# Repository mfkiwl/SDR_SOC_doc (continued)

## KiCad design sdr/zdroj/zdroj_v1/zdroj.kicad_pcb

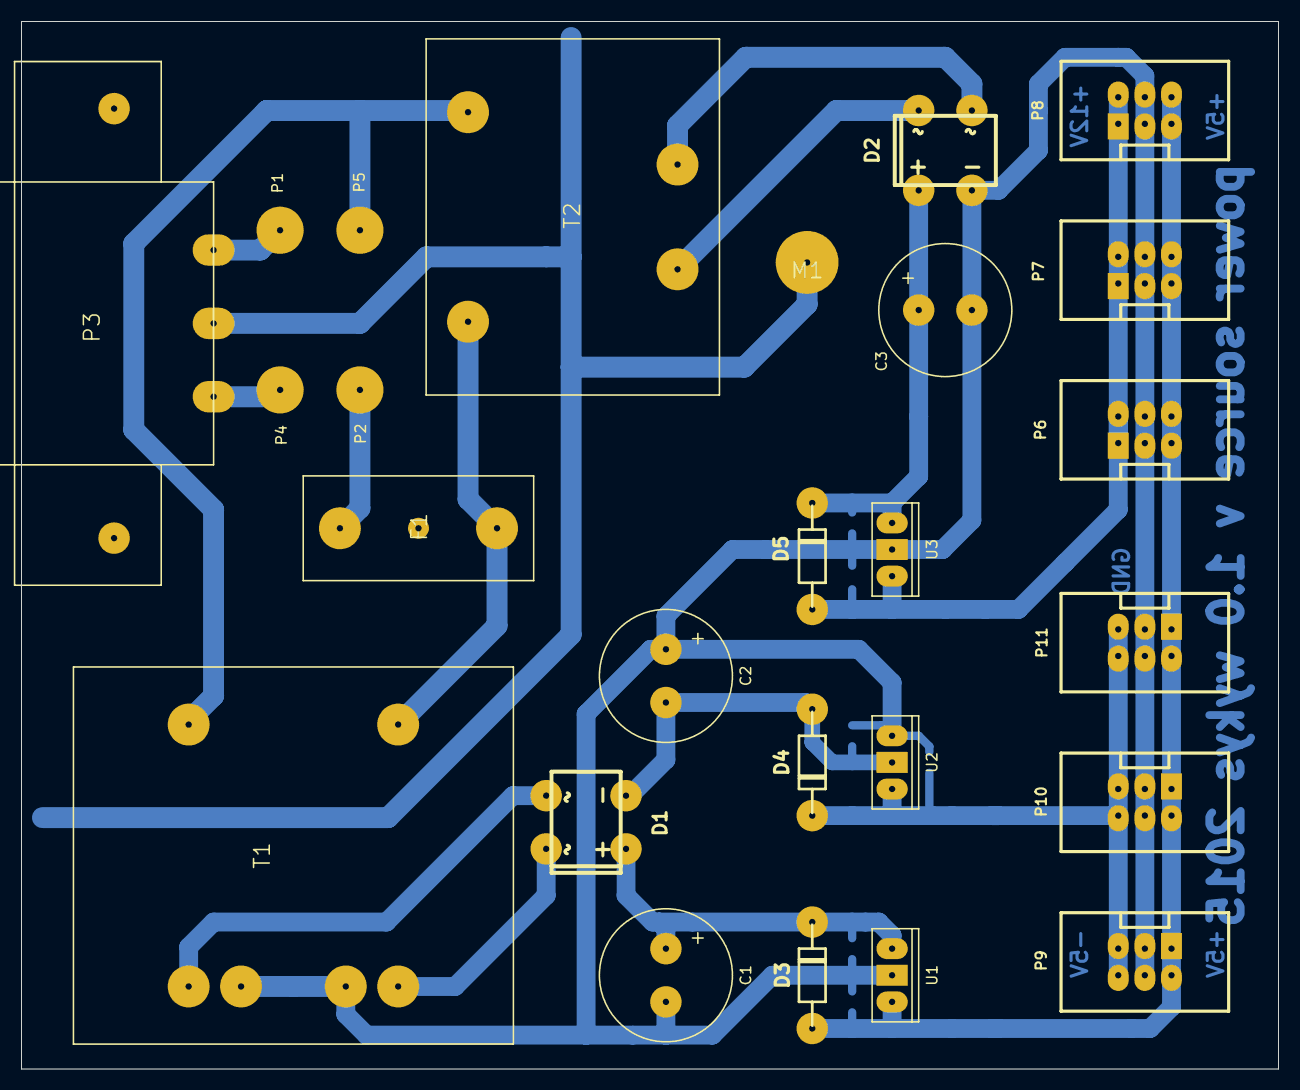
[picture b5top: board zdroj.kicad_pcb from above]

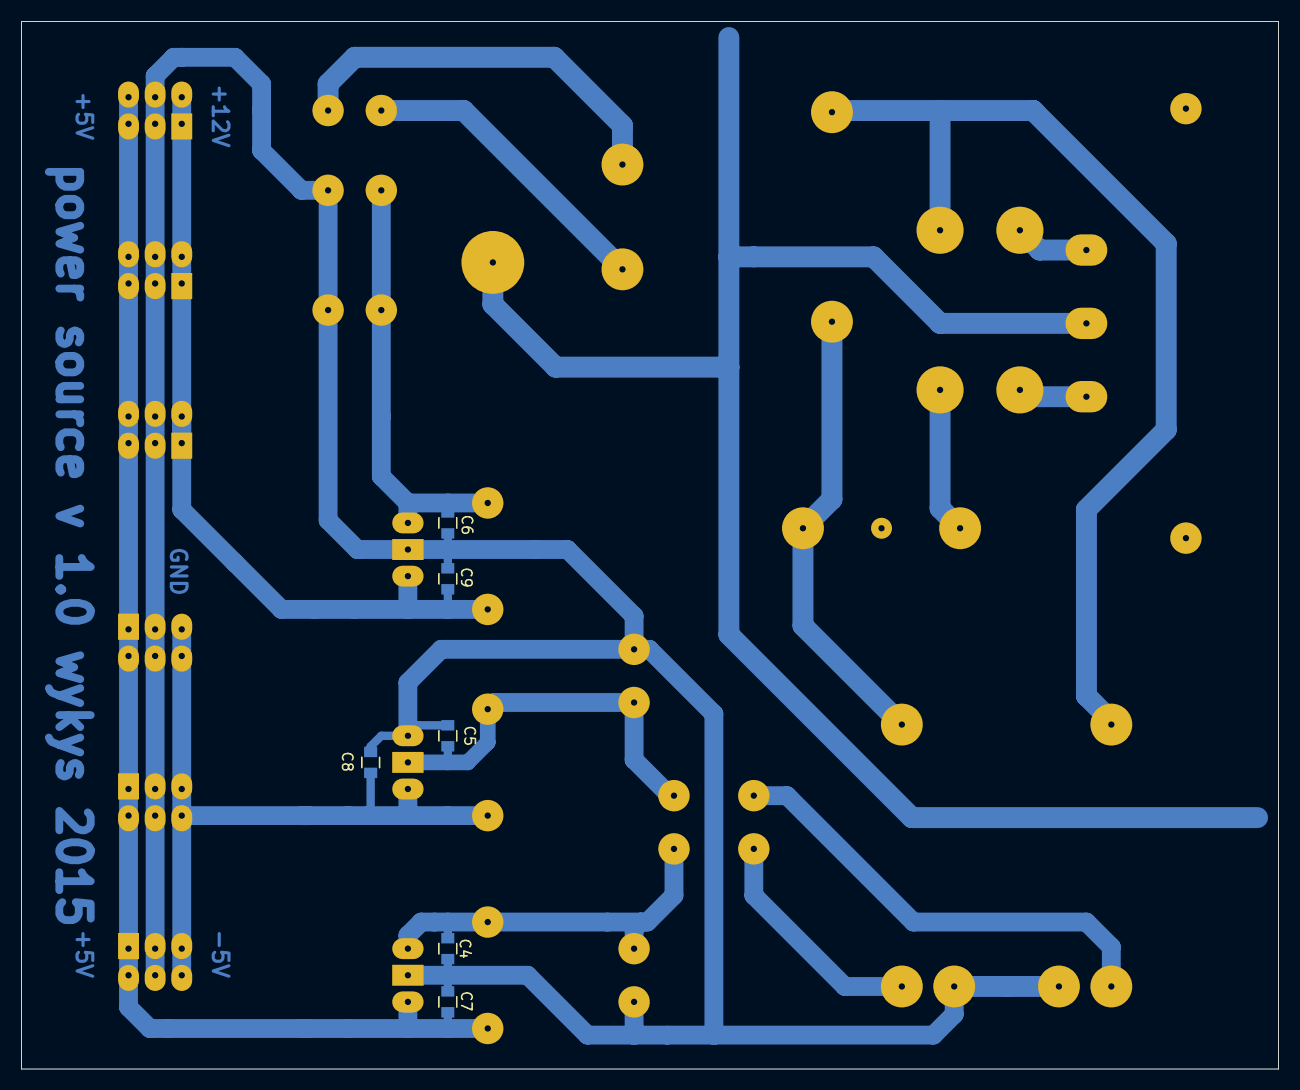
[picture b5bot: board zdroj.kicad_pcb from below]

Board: 2 copper layers, 120.0 x 100.0 mm, 32 parts (6 on the bottom side), 17 nets.

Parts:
C1, C2, C3: 470u/100V; Elko_vert_25x12.5mm_RM5_CopperClear
C4, C5, C6, C7, C8, C9: 100n; C_0805
D1, D2: DB104; bridge_DFM
D3, D4, D5: D_Schottky; diode_do41
F1: 1A/230V; fuse_socket
M1: M3
P1: L1; SolderWirePad_single_2mmDrill
P2: L2; SolderWirePad_single_2mmDrill
P3: CON_EU_PANEL
P4: N1; SolderWirePad_single_2mmDrill
P5: N2; SolderWirePad_single_2mmDrill
P6, P7, P8, P9, P10, P11: MLW6; vasch_strip_3x2
T1: TRANSFO2; BV_EI_382
T2: TRANSFO; BV_EI_303
U1: 7805; LM78XXV
U2: 7905; LM79XXV
U3: LM7812; LM78XXV

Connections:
+5V: C7.1, D3.1, P6.5, P6.6, P7.5, P7.6, P8.5, P8.6, P9.1, P9.2, P10.1, P10.2, P11.1, P11.2, U1.VO
+12V: C9.1, D5.1, P6.1, P6.2, P7.1, P7.2, P8.1, P8.2, U3.VO
-5V: C8.2, D4.2, P9.5, P9.6, P10.5, P10.6, P11.5, P11.6, U2.VO
Earth: M1.1, P3.2
GND: C1.2, C2.1, C3.2, C4.2, C5.1, C6.2, C7.2, C8.1, C9.2, D2.4, P6.3, P6.4, P7.3, P7.4, P8.3, P8.4, P9.3, P9.4, P10.3, P10.4, P11.3, P11.4, T1.4, T1.5, U1.GND, U2.GND, U3.GND
unnamed: C1.1, C4.1, D1.1, D3.2, U1.VI
unnamed: C2.2, C5.2, D1.4, D4.1, U2.VI
unnamed: C3.1, C6.1, D2.1, D5.2, U3.VI
unnamed: D1.2, T1.3
unnamed: D1.3, T1.6
unnamed: D2.2, T2.3
unnamed: D2.3, T2.4
unnamed: F1.1, P2.1
unnamed: F1.2, T1.1, T2.2
unnamed: P1.1, P3.1
unnamed: P3.3, P4.1
unnamed: P5.1, T1.2, T2.1

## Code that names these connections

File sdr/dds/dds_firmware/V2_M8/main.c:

/*
 * main.c
 *
 *  Created on: Mar 1, 2015
 *      Author: wykys
 */



#include <avr/io.h>
#define F_CPU 11059000UL
#include <util/delay.h>

#define DDS_FQ_UD	PD7
#define DDS_W_CLK	PD6
#define DDS_LOAD	PD5
#define DDS_RESET	PD4

#define LCD_RS		PB0
#define LCD_EN		PB1
// =========================================
#define FQ_UD1 (PORTD |= (1<<DDS_FQ_UD))
#define FQ_UD0 (PORTD &= ~(1<<DDS_FQ_UD))
// =========================================
#define W_CLK1 (PORTD |= (1<<DDS_W_CLK))
#define W_CLK0 (PORTD &= ~(1<<DDS_W_CLK))
// =========================================
#define LOAD1 (PORTD |= (1<<DDS_LOAD))
#define LOAD0 (PORTD &= ~(1<<DDS_LOAD))
// =========================================
#define RESET1 (PORTD |= (1<<DDS_RESET))
#define RESET0 (PORTD &= ~(1<<DDS_RESET))
// =========================================


// =========================================
#define LCD_RS1 (PORTB |= (1<<LCD_RS))
#define LCD_RS0 (PORTB &= ~(1<<LCD_RS))
// =========================================
#define LCD_EN1 (PORTB |= (1<<LCD_EN))
#define LCD_EN0 (PORTB &= ~(1<<LCD_EN))
// =========================================
#define LCD_BUS PORTC

const uint8_t ctable[] = {
		0b000110000,	// 0
		0b000110001,	// 1
		0b000110010,	// 2
		0b000110011,	// 3
		0b000110100,	// 4
		0b000110101,	// 5
		0b000110110,	// 6
		0b000110111,	// 7
		0b000111000,	// 8
		0b000111001,	// 9
		0b010010000,	// ' '
		0b001001000,	// H
		0b001111010,	// z
		0b001100110,	// f
		0b001110011,	// s
		0b000111010		// :
};

void LCD_NibleCom(uint8_t data, uint8_t time)
{
	uint8_t A0, A1, A2, A3;

	A0 = (data & 0b1000) >> 3;
	A1 = (data & 0b0100) >> 1;
	A2 = (data & 0b0010) << 1;
	A3 = (data & 0b0001) << 3;

	LCD_EN0;
	LCD_RS0;
	LCD_BUS = A3 | A2 | A1 | A0;
	LCD_EN1;
	LCD_EN0;

	if (time)
		_delay_us(50);
	else
		_delay_ms(2);

	LCD_EN0;
	LCD_RS0;
}

void LCD_NiblePrint(uint8_t data)
{
	uint8_t A0, A1, A2, A3;

	A0 = (data & 0b1000) >> 3;
	A1 = (data & 0b0100) >> 1;
	A2 = (data & 0b0010) << 1;
	A3 = (data & 0b0001) << 3;

	LCD_EN0;
	LCD_RS1;
	LCD_BUS = A3 | A2 | A1 | A0;
	LCD_EN1;
	LCD_EN0;

	_delay_us(50);

	LCD_EN0;
	LCD_RS0;
}

void LCD_Write(uint8_t c)
{
	LCD_NiblePrint((ctable[c] & 0xF0)>>4);
	LCD_NiblePrint(ctable[c] & 0x0F);
}

void LCD_Update(double freq, double step)
{
	// smazat
	//LCD_Com(0b00000001);
	LCD_NibleCom(0b0000,0);
	LCD_NibleCom(0b0001,0);

	// zápis 1. řádek
	//LCD_Com(0b10000000);
	LCD_NibleCom(0b1000,1);
	LCD_NibleCom(0b0000,1);

	uint32_t i,j;
	int32_t f = (int32_t) freq;
	int32_t s = (int32_t) step;
	uint8_t flag = 1;

	f =	(f-6000000 < 0) ? 6000000-f : f-6000000;

	LCD_Write(13);
	LCD_Write(15);
	LCD_Write(10);

	for (i=0, j=10000000; i<8; i++, j/=10)
	{
		if (f/j)
		{
			flag = 0;
			LCD_Write(f/j);
			f -= j*(f/j);
		}
		else
			if (f && flag)
				LCD_Write(10);
			else
				LCD_Write(0);
		// formatovaci mezery
		if (i == 1 || i == 4)
			LCD_Write(10);
	}

	LCD_Write(10);
	LCD_Write(11);
	LCD_Write(12);



	// zápis 2. řádek
	//LCD_Com(0b11000000);
	LCD_NibleCom(0b1100,1);
	LCD_NibleCom(0b0000,1);

	LCD_Write(14);
	LCD_Write(15);
	LCD_Write(10);

	flag = 1;
	for (i=0, j=10000000; i<8; i++, j/=10)
	{
		if (s/j)
		{
			flag = 0;
			LCD_Write(s/j);
			s -= j*(s/j);
		}
		else
			if (s && flag)
				LCD_Write(10);
			else
				LCD_Write(0);

		// formatovaci mezery
		if (i == 1 || i == 4)
			LCD_Write(10);
	}

	LCD_Write(10);
	LCD_Write(11);
	LCD_Write(12);

}

void LCD_Init(void)
{
	// inicializace

	_delay_ms(2000);

	LCD_NibleCom(0b0010,1);
	LCD_NibleCom(0b0010,1);
	LCD_NibleCom(0b1011,1);
	LCD_NibleCom(0b0000,1);
	LCD_NibleCom(0b1111,1);
	LCD_NibleCom(0b0000,0);
	LCD_NibleCom(0b0001,0);
}

void dds_Reset(void)
{
	// set output pin value
	RESET0;
	FQ_UD0;
	W_CLK0;
	LOAD0;

	// reset AD9850
	RESET0;
	_delay_ms(5);
	RESET1;
	_delay_ms(5);
	RESET0;
	_delay_ms(5);

	//serial mode enable
	W_CLK0;
	W_CLK1;
	W_CLK0;

	FQ_UD0;
	FQ_UD1;
	FQ_UD0;
}

void dds_SendBit(uint8_t bit)
{
	(bit) ? LOAD1 : LOAD0;
	W_CLK0;
	W_CLK1;
	W_CLK0;
}

void dds_SetFreq(double freq) // frequency = out frequency in Hz
{
	uint32_t phase;
	phase = (freq*0xFFFFFFFF)/100000000UL;

	uint8_t i;
	for (i=0; i<32; i++)
		dds_SendBit((phase>>i) & 1);

	for (i=0; i<8; i++)
		dds_SendBit(0);

	FQ_UD0;
	FQ_UD1;
	FQ_UD0;

}

int main(void)
{
	DDRB |= (1<<LCD_RS) | (1<<LCD_EN); // L in H out
	PORTB |= (1<<PB2);

	DDRC = 0xFF; // L in H out
	PORTC = 0x00;

	DDRD |= (1<<DDS_FQ_UD) | (1<<DDS_W_CLK) | (1<<DDS_LOAD) | (1<<DDS_RESET);
	PORTD |= (1<<PD2) | (1<<PD3);





	// on PD2 is ENC
	// on PD3 is ENC

	double f = 20000000;
	double step = 10000;



	uint8_t state, old_state;
	uint8_t mode = 0;

	dds_Reset();
    dds_SetFreq(f);

    LCD_Init();
    LCD_Update(f, step);


    state = (((PIND & (1<<PD3)) | (PIND & (1<<PD2))) >> 2);


    while(1)
    {
    	while ((state == (((PIND & (1<<PD3)) | (PIND & (1<<PD2))) >> 2)) || ((PINB & (1<<PB2)) == 1)) // počkej dokud se neotočí
    		;

    	// kontorla stisku tlačítka
		if ((PINB & (1<<PB2)) == 0)
		{
			mode = (mode) ? 0 : 1;

			while ((PINB & (1<<PB2)) == 0)
				;

		}
		else // není stusknuto tlačítko
		{
			old_state = state; // přesuň předchozí stav do historie
			state = (((PIND & (1<<PD3)) | (PIND & (1<<PD2))) >> 2); // ulož nový stav

			// vyhodnocení změny
			//if ( (old_state == 3 && state == 2) || (old_state == 2 && state == 0) ||  (old_state == 0 && state == 1) || (old_state == 1 && state == 3) ) //otočení směr plus
			if ( (old_state == 3 && state == 2)) //otočení směr plus
			{


				if (mode == 0) // mód lazení frekvence
				{
					if (f+step <= 50000000)
					{
						f += step;
						dds_SetFreq(f);
						LCD_Update(f, step);
					}
				}
				else // mód změny kroku lazení
					if (step*10 <= 10000000)
					{
						step *= 10;
						LCD_Update(f, step);
					}
			}
			// kvůli mezipozicím enkodéru ingnorujeme 3 ze 4 stavů
			else if ((old_state == 2 && state == 0) ||  (old_state == 0 && state == 1) || (old_state == 1 && state == 3) )
				;
			else if ((old_state == 0 && state == 2) ||  (old_state == 1 && state == 0) || (old_state == 3 && state == 1) )
				;
			else // otočení směr minus
			{


				if (mode == 0) // mód lazení frekvence
				{
					if (f-step >= 1000000)
					{
						f -= step;
						dds_SetFreq(f);
						LCD_Update(f, step);
					}
				}
				else // mód změny kroku lazení
					if (step/10 >= 1)
					{
						step /= 10;
						LCD_Update(f, step);
					}
			}
		}
    }

}

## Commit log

2016-03-18 :boom::camel: Added .gitattributes & .gitignore files
2016-03-18 SDR
    dlouhodobka
